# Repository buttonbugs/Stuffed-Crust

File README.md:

# Stuffed Crust

This repository contains the code for Wildcat Robotics' team Stuffed Crust. This is a fork of the open source melty brain code, openmelt [^1], with improved translational drift algorithm, adapted watchdog [^2] for [Teensy 4.0](https://www.pjrc.com/store/teensy40.html) and some other changes specific to Stuffed Crust's design.

## Preview

https://github.com/user-attachments/assets/2b465f3a-5d59-4c2d-9435-344acd4d646b

### References

[^1]: R. Olson and M. Schoppert, [“nothinglabs/openmelt2,”](https://github.com/nothinglabs/openmelt2/) July 2026. original-date: 2023-03-04T03:05:36Z.

[^2]: A. Brewer and S. Nobs, [“tonton81/WDT t4,”](https://github.com/tonton81/WDT_T4) Feb. 2026. original-date: 2020-01-
26T16:30:28Z.

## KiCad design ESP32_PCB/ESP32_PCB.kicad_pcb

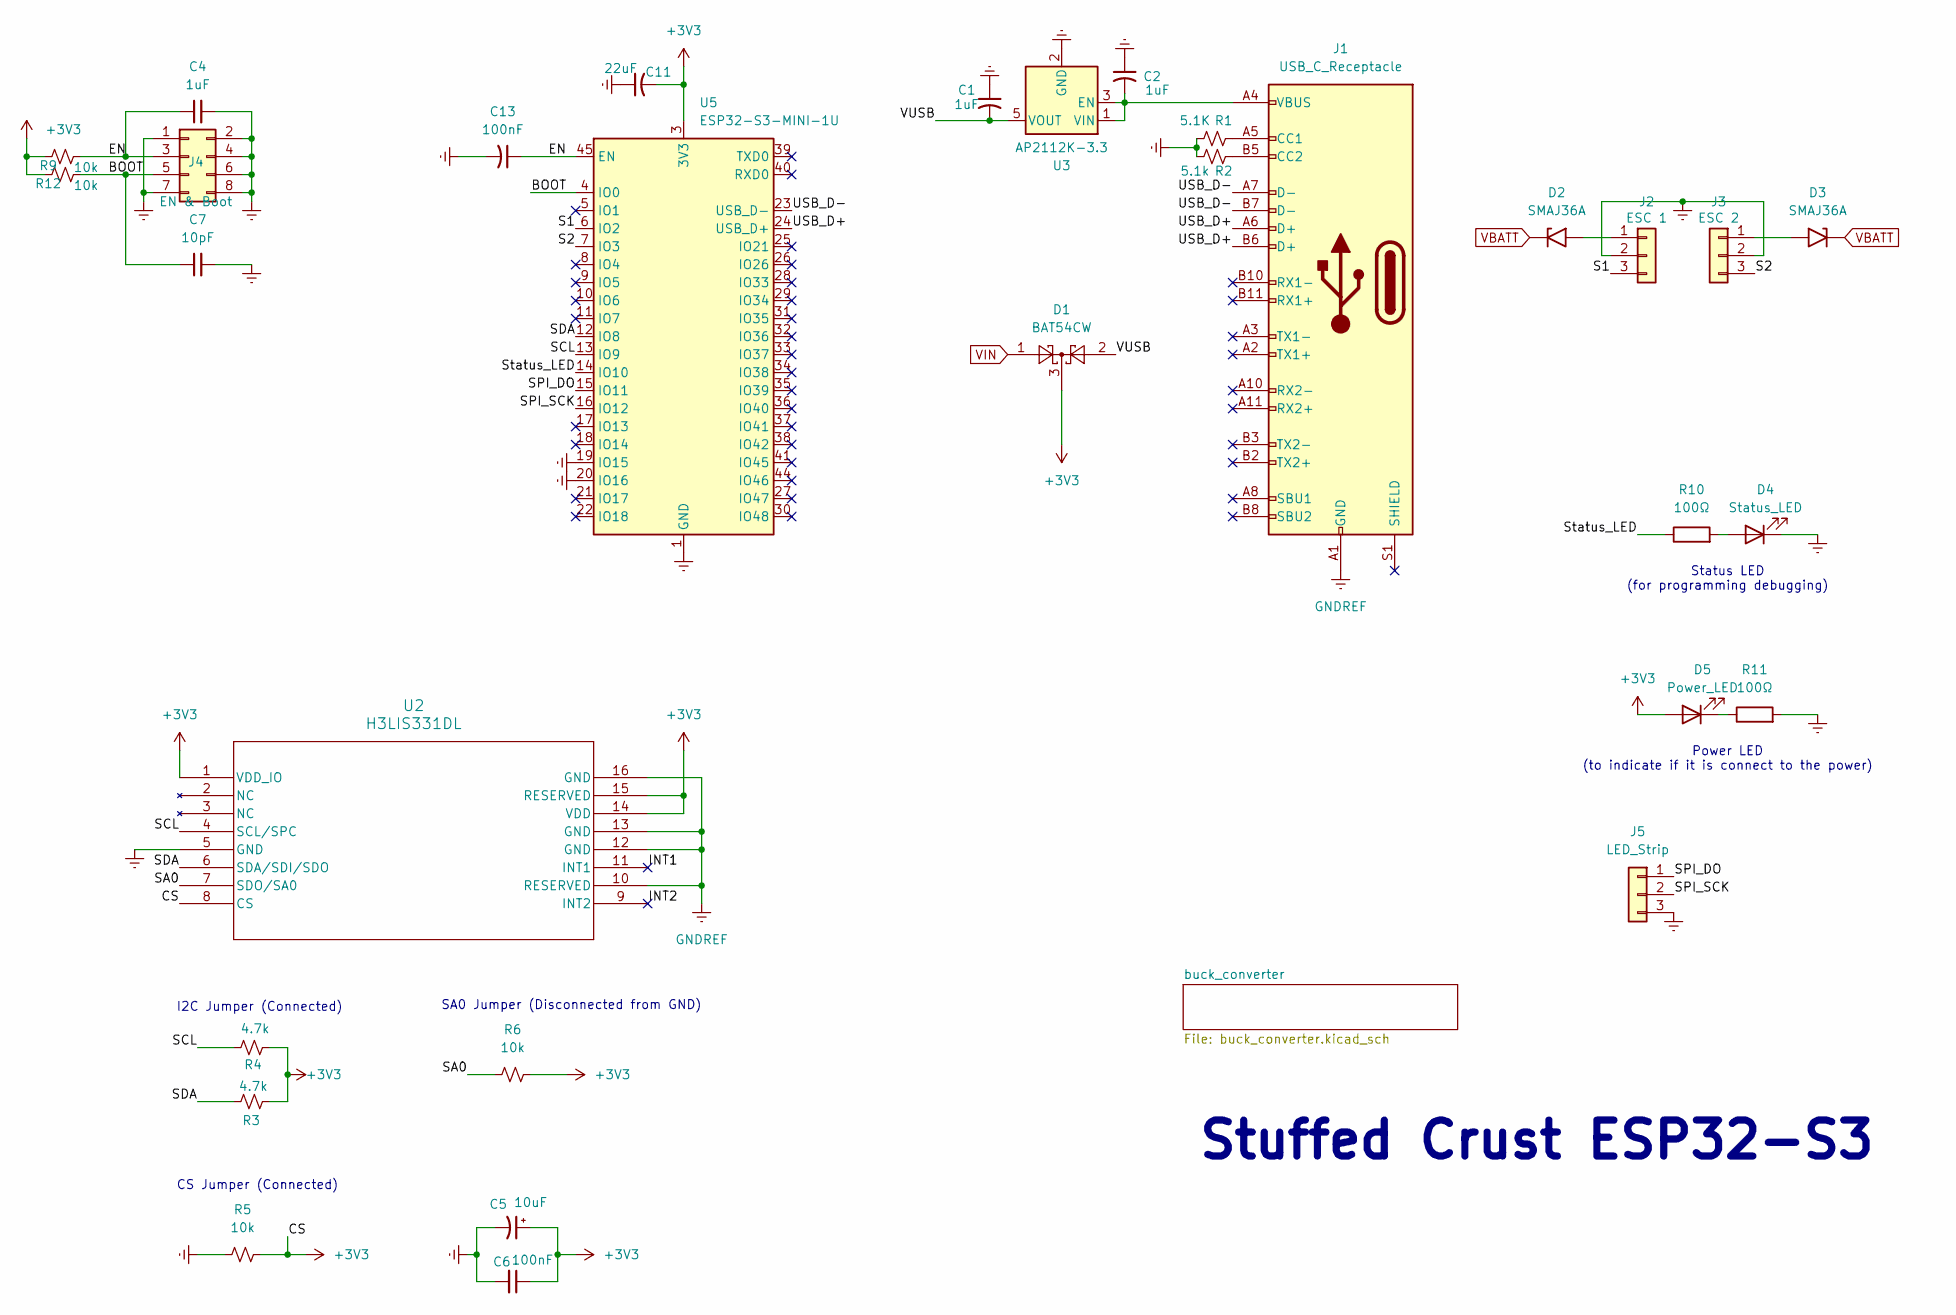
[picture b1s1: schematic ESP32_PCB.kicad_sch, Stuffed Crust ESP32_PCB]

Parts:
C1, C2, C4: 1uF; C_0603_1608Metric; LCSC PN C15849
C5: 10uF; CP_EIA-3216-18_Kemet-A; LCSC PN C7171
C6, C13: 100nF; C_0603_1608Metric; LCSC PN C14663
C7: 10pF; C_0603_1608Metric; LCSC PN C106245
C11: 22uF; C_0603_1608Metric; LCSC PN C86295
D1: BAT54CW; SOT-323_SC-70; LCSC PN C192144
D2, D3: SMAJ36A; D_SMA; LCSC PN C148232
D4: Status_LED; LED_0603_1608Metric; LCSC PN C19273151
D5: Power_LED; LED_0603_1608Metric; LCSC PN C19171390
J1: USB_C_Receptacle; USB_C_Receptacle_Molex_105450-0101; LCSC PN C134092
J2: ESC 1; 3_Pin
J3: ESC 2; 3_Pin
J4: EN & Boot; PinHeader_2x04_P2.54mm_Vertical; LCSC PN C32713277
J5: LED_Strip
R1: 5.1K; R_0603_1608Metric; LCSC PN C2907044
R2: 5.1k; R_0603_1608Metric; LCSC PN C2907044
R3, R4: 4.7k; R_0603_1608Metric; LCSC PN C99782
R5, R6, R9, R12: 10k; R_0603_1608Metric; LCSC PN C98220
R10, R11: 100Ω; R_0603_1608Metric; LCSC PN C105588
U2: H3LIS331DL; TFLGA16_3X3X1_STM; LCSC PN C2655074
U3: AP2112K-3.3; SOT-23-5; LCSC PN C23380830
U5: ESP32-S3-MINI-1U; ESP32-S2-MINI-1U; LCSC PN C2980299

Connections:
+3V3: C5.1, C6.1, C11.2, D1.3, D5.2 (A), R3.1, R4.1, R5.2, R6.2, R9.2, R12.2, U2.1 (VDD_IO), U2.8 (CS), U2.14 (VDD), U2.15 (RESERVED), U5.3 (3V3)
/BOOT: C7.1, J4.5, R12.1, U5.4 (IO0)
/EN: C4.1, C13.1, J4.3, R9.1, U5.45 (EN)
/INT1: U2.11 (INT1)
/INT2: U2.9 (INT2)
/S1: J2.3, U5.6 (IO2)
/S2: J3.3, U5.7 (IO3)
/SA0: R6.1, U2.7 (SDO/SA0)
/SCL: R4.2, U2.4 (SCL/SPC), U5.13 (IO9)
/SDA: R3.2, U2.6 (SDA/SDI/SDO), U5.12 (IO8)
/SPI_DO: J5.1, U5.15 (IO11)
/SPI_SCK: J5.2, U5.16 (IO12)
/Status_LED: R10.1, U5.14 (IO10)
/USB_D+: J1.A6 (D+), J1.B6 (D+), U5.24 (USB_D+)
/USB_D-: J1.A7 (D-), J1.B7 (D-), U5.23 (USB_D-)
/VUSB: C1.2, D1.2, U3.5 (VOUT)
GNDREF: C1.1, C2.1, C4.2, C5.2, C6.2, C7.2, C11.1, C13.2, D4.1 (K), J1.A1 (GND), J1.A12 (GND), J1.B1 (GND), J1.B12 (GND), J2.2, J3.2, J4.1, J4.2, J4.4, J4.6, J4.7, J4.8, J5.3, R1.1, R2.1, R5.1, R11.2, U2.5 (GND), U2.10 (RESERVED), U2.12 (GND), U2.13 (GND), U2.16 (GND), U3.2 (GND), U5.1 (GND), U5.2 (GND), U5.19 (IO15), U5.20 (IO16), U5.42 (GND), U5.43 (GND), U5.46 (GND), U5.47 (GND), U5.48 (GND), U5.49 (GND), U5.50 (GND), U5.51 (GND), U5.52 (GND), U5.53 (GND), U5.54 (GND), U5.55 (GND), U5.56 (GND), U5.57 (GND), U5.58 (GND), U5.59 (GND), U5.60 (GND), U5.61 (GND), U5.62 (GND), U5.63 (GND), U5.64 (GND), U5.65 (GND); also elsewhere on the board
unnamed: D2.2 (A2), J2.1
unnamed: D3.2 (A2), J3.1
unnamed: D4.2 (A), R10.2
unnamed: D5.1 (K), R11.1
unnamed: J1.A5 (CC1), R1.2
unnamed: J1.B5 (CC2), R2.2
unnamed: C2.2, J1.A4 (VBUS), J1.A9 (VBUS), J1.B4 (VBUS), J1.B9 (VBUS), U3.1 (VIN), U3.3 (EN)
VBATT: D2.1 (A1), D3.1 (A1); also elsewhere on the board
VIN: D1.1; also elsewhere on the board

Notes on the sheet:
Power LED (to indicate if it is connect to the power)
Stuffed Crust ESP32-S3
Status LED (for programming debugging)
CS Jumper (Connected)
I2C Jumper (Connected)
SA0 Jumper (Disconnected from GND)

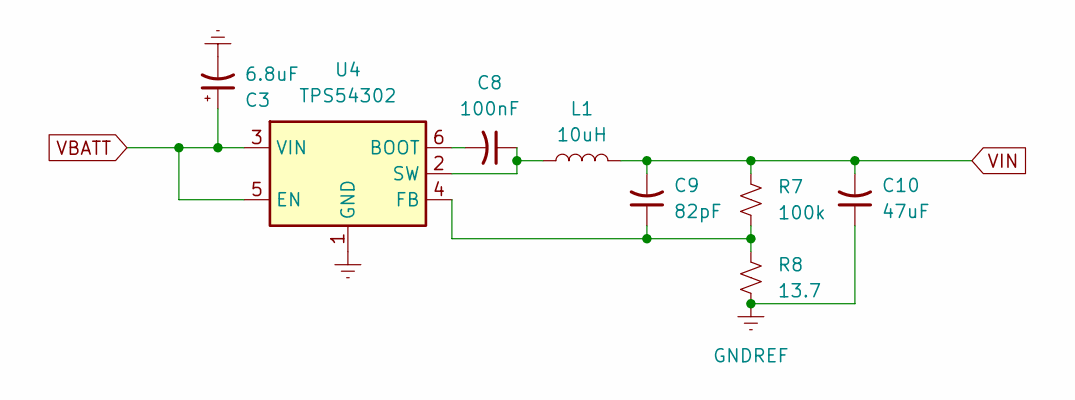
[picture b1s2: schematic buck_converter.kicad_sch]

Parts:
C3: 6.8uF; CP_EIA-3216-18_Kemet-A; LCSC PN C444749
C8: 100nF; C_0603_1608Metric; LCSC PN C14663
C9: 82pF; C_0603_1608Metric; LCSC PN C1683
C10: 47uF; C_0805_2012Metric; LCSC PN C16780
L1: 10uH; L_APV_APH0630; LCSC PN C5349698
R7: 100k; R_0805_2012Metric; LCSC PN C7319379
R8: 13.7; R_0805_2012Metric; LCSC PN C409962
U4: TPS54302; TSOT-23-6; LCSC PN C311983

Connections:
GNDREF: C3.2, C10.1, R8.2, U4.1 (GND); also elsewhere on the board
unnamed: C8.2, U4.6 (BOOT)
unnamed: C9.1, R7.2, R8.1, U4.4 (FB)
unnamed: C8.1, L1.1, U4.2 (SW)
VBATT: C3.1, U4.3 (VIN), U4.5 (EN); also elsewhere on the board
VIN: C9.2, C10.2, L1.2, R7.1; also elsewhere on the board

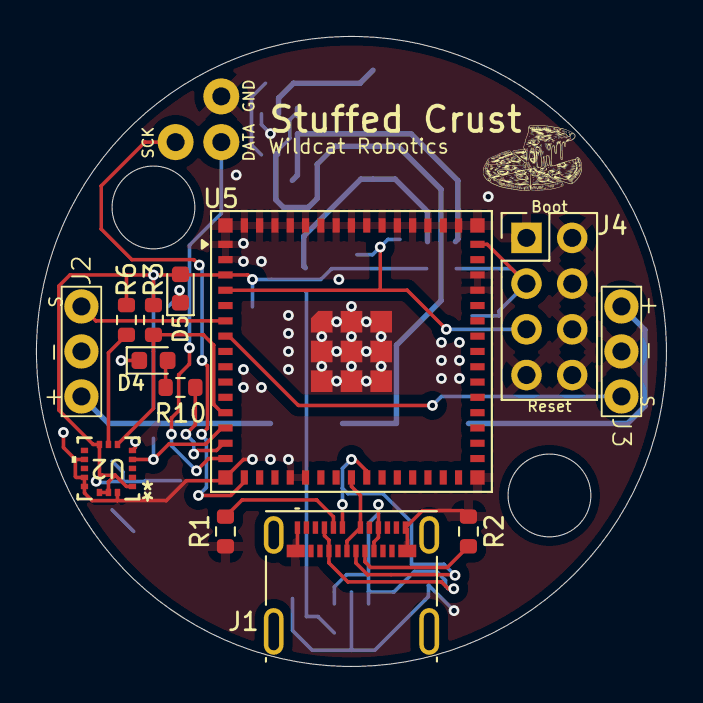
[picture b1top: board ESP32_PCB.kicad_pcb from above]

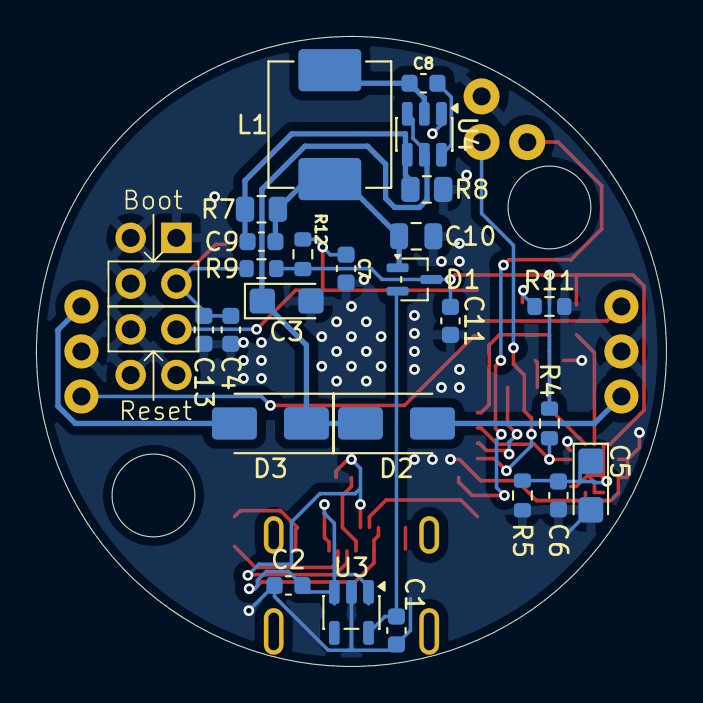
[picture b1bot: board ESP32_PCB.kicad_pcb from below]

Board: 2 copper layers, 35.0 x 35.0 mm, 39 parts (25 on the bottom side), 27 nets.

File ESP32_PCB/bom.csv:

Qty,Comment,DNP,Exclude from BOM,Exclude from Board,Designator,Footprint,LCSC PN,Datasheet
3,1uF,,,,"C1,C2,C4",Capacitor_SMD:C_0603_1608Metric,C15849,~
1,6.8uF,,,,C3,Capacitor_Tantalum_SMD:CP_EIA-3216-18_Kemet-A,C444749,~
1,10uF,,,,C5,Capacitor_Tantalum_SMD:CP_EIA-3216-18_Kemet-A,C7171,~
3,100nF,,,,"C6,C8,C13",Capacitor_SMD:C_0603_1608Metric,C14663,~
1,10pF,,,,C7,Capacitor_SMD:C_0603_1608Metric,C106245,~
1,82pF,,,,C9,Capacitor_SMD:C_0603_1608Metric,C1683,
1,47uF,,,,C10,Capacitor_SMD:C_0805_2012Metric,C16780,
1,22uF,,,,C11,Capacitor_SMD:C_0603_1608Metric,C86295,
1,BAT54CW,,,,D1,Package_TO_SOT_SMD:SOT-323_SC-70,C192144,https://assets.nexperia.com/documents/data-sheet/BAT54W_SER.pdf
2,SMAJ36A,,,,"D2,D3",Diode_SMD:D_SMA,C148232,https://www.littelfuse.com/media?resourcetype=datasheets&ite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
1,Status_LED,,,,D4,LED_SMD:LED_0603_1608Metric,C19273151,~
1,Power_LED,,,,D5,LED_SMD:LED_0603_1608Metric,C19171390,~
1,USB_C_Receptacle,,,,J1,Connector_USB:USB_C_Receptacle_Molex_105450-0101,C134092,https://www.usb.org/sites/default/files/documents/usb_type-c.zip
1,ESC 1,,,,J2,ESC_Connectors:3_Pin,,~
1,ESC 2,,,,J3,ESC_Connectors:3_Pin,,~
1,EN & Boot,,,,J4,Connector_PinHeader_2.54mm:PinHeader_2x04_P2.54mm_Vertical,C32713277,~
1,LED_Strip,,,,J5,ESC_Connectors:LED_Strip,,~
1,10uH,,,,L1,Inductor_SMD:L_APV_APH0630,C5349698,~
1,5.1K,,,,R1,Resistor_SMD:R_0603_1608Metric,C2907044,~
1,5.1k,,,,R2,Resistor_SMD:R_0603_1608Metric,C2907044,~
2,4.7k,,,,"R3,R4",Resistor_SMD:R_0603_1608Metric,C99782,~
4,10k,,,,"R5,R6,R9,R12",Resistor_SMD:R_0603_1608Metric,C98220,~
1,100k,,,,R7,Resistor_SMD:R_0805_2012Metric,C7319379,~
1,13.7,,,,R8,Resistor_SMD:R_0805_2012Metric,C409962,~
2,100Ω,,,,"R10,R11",Resistor_SMD:R_0603_1608Metric,C105588,~
1,H3LIS331DL,,,,U2,accelerometer:TFLGA16_3X3X1_STM,C2655074,https://www.st.com/resource/en/datasheet/h3lis331dl.pdf
1,AP2112K-3.3,,,,U3,Package_TO_SOT_SMD:SOT-23-5,C23380830,https://www.diodes.com/assets/Datasheets/AP2112.pdf
1,TPS54302,,,,U4,Package_TO_SOT_SMD:SOT-563,C50310967,http://www.ti.com/lit/ds/symlink/tps54302.pdf
1,ESP32-S3-MINI-1U,,,,U5,RF_Module:ESP32-S2-MINI-1U,C2980299,https://www.espressif.com/sites/default/files/documentation/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

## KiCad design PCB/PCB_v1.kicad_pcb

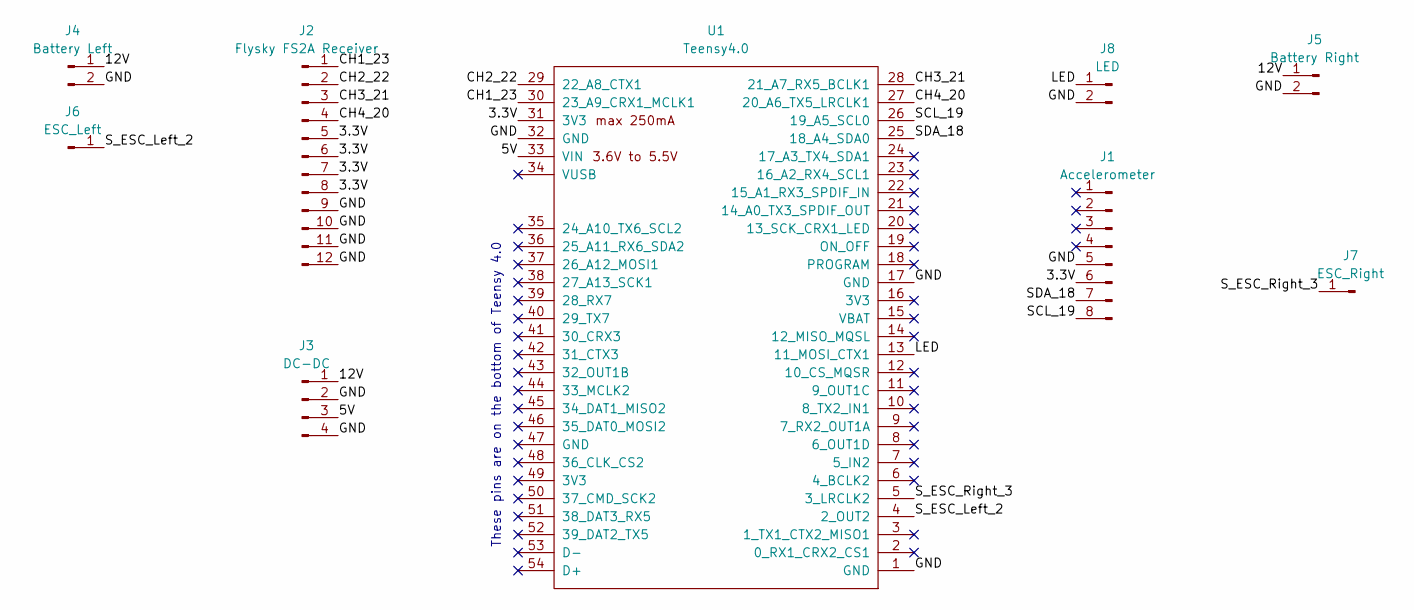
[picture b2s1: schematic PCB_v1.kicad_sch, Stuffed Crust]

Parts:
J1: Accelerometer
J2: Flysky FS2A Receiver; Flysky_FS2A_Receiver
J3: DC-DC; DC_DC
J4: Battery Left; Battery
J5: Battery Right; Battery
J6: ESC_Left; ESC
J7: ESC_Right; ESC
J8: LED
U1: Teensy4.0; Teensy40

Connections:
/3.3V: J1.6, J2.5, J2.6, J2.7, J2.8, U1.31 (3V3)
/5V: J3.3, U1.33 (VIN)
/12V: J3.1, J4.1, J5.1
/CH1_23: J2.1, U1.30 (23_A9_CRX1_MCLK1)
/CH2_22: J2.2, U1.29 (22_A8_CTX1)
/CH3_21: J2.3, U1.28 (21_A7_RX5_BCLK1)
/CH4_20: J2.4, U1.27 (20_A6_TX5_LRCLK1)
/GND: J1.5, J2.9, J2.10, J2.11, J2.12, J3.2, J3.4, J4.2, J5.2, J8.2, U1.1 (GND), U1.17 (GND), U1.32 (GND)
/LED: J8.1, U1.13 (11_MOSI_CTX1)
/SCL_19: J1.8, U1.26 (19_A5_SCL0)
/SDA_18: J1.7, U1.25 (18_A4_SDA0)
/S_ESC_Left_2: J6.1, U1.4 (2_OUT2)
/S_ESC_Right_3: J7.1, U1.5 (3_LRCLK2)

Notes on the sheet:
These pins are on the bottom of Teensy 4.0

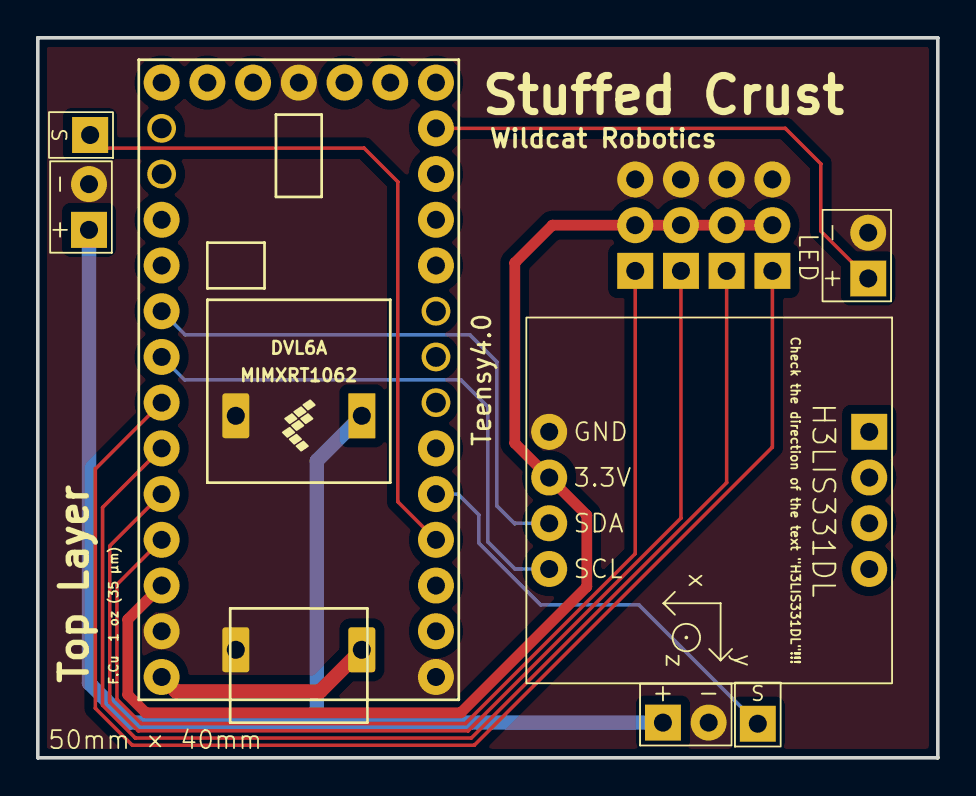
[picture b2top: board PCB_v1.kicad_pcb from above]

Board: 2 copper layers, 50.0 x 40.0 mm, 9 parts (0 on the bottom side), 13 nets.

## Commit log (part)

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2026-01-19 Add new to-dos in README.md
2026-01-19 Remove an item from README to-do
2026-01-19 Wiring.png
2026-01-19 Add wiring diagram image to README.md
    Added image reference for wiring diagram.
2026-01-21 Update README.md
    Update ACCEL_I2C_ADDRESS in TODO section to reflect Sparkfun default.
2026-01-22 Update README.md
    Pin configs in `melty_config.h` should be changed.
2026-01-23 fix: arduino imports, pin assignments
2026-01-23 update rc pulse lengths
2026-01-23 fix: warnings
2026-01-23 rename leftright to revolution
2026-01-23 remove extra readme
2026-01-24 Update README.md
    Add watchdog library link in README.md
2026-01-24 Import WDT_T4 watchdog
2026-01-24 Rename WDT_T4
2026-01-24 Rename WDT_T4 Back
2026-01-24 add fourth channel for revolution and rename leftright to revolution
2026-01-24 Add watchdog; Add rc_forback `rc_get_leftright();` in `rc_handler.h`
2026-01-24 initial translation
2026-01-24 Watchdog testing finished
2026-01-31 Create PCB; import Teensy 4.0 symbol
2026-01-31 Finish KiCad Schematic
2026-02-01 Import Teensy Footprints
2026-02-01 Create Footprint for DC_DC
2026-02-01 Update DC_DC Footprint
2026-02-01 Add and Link the Footprint of Flysky FS2A Receiver
2026-02-01 Add LED Connector
2026-02-01 Finish the schematics and footprints of ESC, LED and Battery
2026-02-01 Accelerometer Footprint
2026-02-01 Fix the layer issue in ESC footprint
2026-02-01 Put components onto PCB
2026-02-01 Fix DC_DC Footprint
2026-02-01 Add Teensy-backups to .gitignore
2026-02-01 Remove backup files
2026-02-01 Put DC_DC back to the front layer; change the PCB layout
2026-02-01 PCB Finished
2026-02-01 Update PCB Appearance
2026-02-01 Change the Text on Silkscreen
2026-02-02 Separate GND (for signal) and GND_BT (for high current); make bigger holes for high current wires
2026-02-02 Fix the GND fill
2026-02-02 Update 3D Model
2026-02-02 Remove the small "GND" from ESC
2026-02-03 Only Keep S Pins for ESCs
2026-02-07 gerber and drill files
2026-02-07 arrange files
2026-02-07 Update PCB Layout (80mm*40mm -> 50mm*40mm)
2026-02-07 Finished PCB Layout
2026-02-07 Fix the Text on the PCB
2026-02-07 Update PCB 3D Model
2026-02-07 start pcb-v2
2026-02-08 pcb-v2
2026-02-17 Increase the pad size of Teensy 4.0
2026-03-01 fix: motor driver to be brushless
2026-03-01 Add low speed mode threshold; create low_speed_set_motor() function
2026-03-01 Split rc_get_forback() into 2 functions: rc_get_forback_value() and rc_get_forback()
    The same for rc_get_leftright()
2026-03-01 Create functions in rc_handler to return joystick ratio
2026-03-01 esp32 pcb
2026-03-02 start pcb
2026-03-02 Finish low speed control codes
2026-03-02 fix pin assignments and add en and boot jumper
2026-03-02 horizontal usb-c
2026-03-02 Increase PCB size
2026-03-02 Add LED pins, correct ESC signal pins
2026-03-03 remove xip files
2026-03-04 tuning
2026-03-15 Add two diodes for VBATT pins
2026-03-15 Replace jumpers on the gyro with direct wires to avoid soldering issue
2026-03-15 Add notes on schematics
2026-03-15 Replace USB_D+ and USB_D- wires with labels
2026-03-15 Update LED footprint
2026-03-15 Remove J2 and J3's SH pins
2026-03-15 Draw tracks for USB_D+ and USB_D- nets
2026-03-15 Upload ESP32-S3-MINI-1U datasheet
2026-03-16 Add tracks for buck converter and USB-C
2026-03-16 Finish EN & Boot header pins layout
2026-03-16 Add tracks for S1, S2 and LED
2026-03-16 Add tracks for gyro
2026-03-16 Place thermal pad vias
2026-03-16 Fix the size of the header pins
2026-03-16 Add labels on PCB
2026-03-16 Add screw holes and Stuffed Crust logo
2026-03-16 Import esp32 3d model
2026-03-16 Adjust esp32 3D model offset
2026-03-16 Export PCB 3D model
2026-03-16 Adjust USB-C 3D model offset
2026-03-16 Export 3D model
2026-03-16 Add 3D model for gyro
2026-03-16 Fix connection error
2026-03-16 Fix GND net isolation
2026-03-20 Change LED portion calculation
2026-03-20 Enable gyro z detection
2026-03-20 Finish motor reverse mode
2026-03-20 Fix extern variable
2026-03-20 Turn off reverse
2026-03-20 Fix resetting bugs
2026-03-20 Add gyro Z offset
2026-03-20 Change radius and lowspeed percent
2026-03-21 add neutral spin
2026-03-21 Fix low speed upside-down leftright
2026-03-21 Enhance precise control
2026-03-21 Change low speed mode forback back to linear
2026-03-21 Remove "1.0f - led_on_portion"
2026-03-21 Switch Gyro to MED_RANGE
2026-03-21 Adjust gyro z offset
2026-03-21 Set motor_coast to 1500
2026-03-21 Disable upside-down
2026-03-22 Add LED strip SPI pin labels
2026-03-23 fix motor driver
2026-03-24 rerouting
2026-03-24 Add LED strip
2026-03-24 Add LED to indicate the power
2026-03-24 Fix unconnected EN pin
2026-03-24 Change the direction of C12 and C13
2026-03-24 Generate gerber files
2026-03-24 Move the text
2026-03-30 New ESP32 led, rc, spin control rough structure
2026-03-30 Change function type in esp32_rc_handler.cpp
2026-04-01 Finish esp32 heading led (not led strip) high speed blinking control
2026-04-01 Fix multiple definition
2026-04-01 Update esp32 heading led (not led strip) calculation
2026-04-01 Import FastLED library for led strip
2026-04-01 Add led strip sector display
2026-04-02 Add a esp32 rc channel for robot facing
2026-04-02 Change the function name in esp32_rc_handler.cpp for clarification
2026-04-02 Add config_mode to esp32_rc_handler
2026-04-02 Add esp32_spin_control revolution motion
2026-04-02 Finish esp32_spin_control translational motion
2026-04-02 add lcsc pn
2026-04-02 fix layout
2026-04-03 Fix LCSC and PCB
2026-04-04 generate BOM, PNP, and update U4
2026-04-04 Finish arrow drawing code
2026-04-05 Optimize arrow drawing performance
2026-04-05 Fix model name
2026-04-05 Fix LED radius calculation
2026-04-06 fix U4
2026-04-07 generating bom and cpl for pcbway
2026-04-11 Old rc compatibility
2026-04-11 Enable ESP32 rc
2026-04-15 add esp32 rc support
2026-04-16 Update radius according to current serial output
2026-04-16 esp32_spin_control first test
2026-04-18 fix: throttle input, esp32 and teensy files; testing
2026-04-18 Fix esp32 rc callback
2026-04-18 Improve spin control: replace while loop with math
2026-04-19 update rc and motor controller
2026-04-21 board changes
2026-04-21 Extern current_frequency
2026-04-21 g values
2026-04-21 Get average g offset
2026-04-21 Improve translational motion calculation
2026-04-22 Debug leftright_ratio and forback_ratio
2026-04-22 Config motor pin
2026-04-22 Update esp32 gyro radius
2026-04-22 Change rc forward to positive
2026-04-22 Update heading LED pin number
2026-04-22 Change config mode button to DPAD_DOWN
2026-04-22 Add rc deadzone
2026-04-22 Display radius
2026-04-22 Display interval_micros
2026-04-22 Config radius mode
2026-04-22 update relay
2026-04-22 fix definition
2026-04-22 Update config speed
2026-04-22 decrease interval
2026-04-23 Enable 0 throttle low speed
2026-04-23 Fix compatibility
2026-04-23 Fix high speed LED
2026-04-24 Add facing toggling (left bumper)
2026-04-24 Enable toggling facing only when accel < 20 G
2026-04-25 Formatting code
2026-04-25 Config LED offset percent
2026-04-25 Use left throttle to control facing down
2026-04-25 Replace functions with extern variables
2026-04-25 Fix wrong facing
2026-04-25 Decrease motor coast
2026-04-25 fixes
2026-04-25 Fix driving direction error (heading led offset still needs to be changed)
2026-04-25 Add rc throttle deadzone
2026-04-26 Measure micros() right before measuring acceleration (trapezoid estimation will be more accurate)
2026-04-29 fix drive
2026-04-30 Add a second LED pin to avoid drawing too much current from one pin
2026-06-06 add esp32s3 cnofig
